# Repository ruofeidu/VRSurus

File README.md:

# VRSurus: A Tangible Virtual-Reality Game for Environmental Protection

### Introduction
We introduce VRSurus, a tangible serious game that aims to inspire children to protect the environment in immersive virtual reality (VR). VRSurus is built upon a physical puppet and a VR head-mounted display (Oculus Rift DK2) to create "tangible virtual animatronics". The player will act as a little elephant called Surus to prevent evil humanbeings from invading the forest. The player is able to use four gestures to cast magical spells: swiping left, swiping right, shaking and jumping. Servos, selonoids and vibration motors will assist with the puppet animation visible to the audience and provide haptic feedback for the player. VRSurus contributes to the HCI, animatronics and tangible computing community by integrating immersive interactive graphics together with gesture recognition and tangible feedback. The game is presented at the UIST 2015 Student Innovation Contest. Video and more details will be publicly available via www.vrsurus.com.

### Story Background
Once upon a time, there was a little elephant named Surus, living happily in a beautiful forest - Green Woodland.
However, in a cloudy day, evil human beings started to invade Green Woodland. They threw garbage everywhere; they used axes to cut down green trees; they even started to construct factories to pollute the air!
The magical elf of Green Woodland assigned you, Surus, to save the forest and rescue the nature! Surus is empowered with the magic of wind, water and fire to destroy the messy garbage, evil lumbermen and destructive factories. 

### Technical Brief
The software is built with WebGL and WebVR, which enables the game to be cross-platform for Oculus Rift and Google Cardboard. We rendered photo-realistic forest environment, GPU-based particle effects as well as skeleton-animated elephants, lumberman and factory. We use HTML5 (WebGL, WebVR, 3D Audio API), Javascript (jQuery & Three.js), GLSL ES (WebGL), PHP (ThinkPHP), MySQL and Java (Processing) to implement the entire system. 

The hardware consists of gyroscope, accelerometer, compass, servos, vibration motors, selonoids, batteries, 3D-printed skeletons and cases. 

### Authors
We the NinjaTerp team! Feel free to visit VRSurus.com for more information!
* Ruofei Du (http://duruofei.com)
   *  [Augmentarium Lab] | [UMIACS] | [University of Maryland, College Park]
   * Team Captain, Graphics (WebGL + WebVR + Model + 3D Audio) and Web Server (PHP + MySQL + Part of Java)
* Liang He (http://lianghe.me)
   * Makeability Lab | [HCIL] | [UMIACS] | [University of Maryland, College Park] 
   * Fabrication (3D Modeling, Printing), Logo, Video and Hardware (Arduino, Java)

### Advisor
* Amitabh Varshney (http://www.cs.umd.edu/~varshney)

### Presentation
The game is presented on UIST 2015 Student Innovation Contest. The project is still work-in-progress for future publications. For now, please cite
> Du, R., He, L. VRSurus: Enhancing Interactivity and Tangibility of Puppets in Virtual Reality. In Proceedings of the 33rd Annual ACM Conference Extended Abstracts on Human Factors in Computing Systems (CHI 16), 8 pages. ACM.

If you find our idea or code useful for your projects.

### How to Use
Feel free to run the entire codebase or build partial code such as only the VR game or only the open-sourced hardware.

##### VRSurus Game
The game is running a webserver with WebGL and WebVR technologies. Here is a step-by-step tutorial:
* Install [XAMPP] to setup a PHP + Apache + MySQL environment.
* Run Apache and MySQL server.
* Clone the git reporsitory and place all code into the XAMPP folder under htdocx/ninjaterp
* Open http://localhost/PHPMyAdmin, Create a new table called vrsurus and import the MySQL data from server/mysql/mysql.sql into the vrsurus table.
* Download the [Oculus Runtime] (v0.6.1 tested, v0.8 should also work) and [Chromium build for WebVR]
* Run http://localhost/ninjaterp using [Chromium build for WebVR]
* Press space on the keyboard to start the tutorial, press enter on the keyboard to start the game.
* You can control Surus using three ways:
    * Keyboard: 1, 2, 3, 4.
    * XBox: A, B, X, Y.
    * Puppet: Swipe left, swipe right, shake, thrust.

If you start the game and observe the scene flying high into the sky, then probably you are not using the correct browser: [Chromium build for WebVR]
### Instructions
##### Gecture
Please close the mouth of the puppet when performing any gesture to attack enemies. Then open the mouth.

##### Wind Spells
Swipe leftward or rightward to clean the garbage.

##### Water Spell
Shake the nose up and down to sweep the lumberman(an) away

##### Fire Spell
Punch forward to destroy the evil factories.

### Code
[Code on Github]

### Technical Challenges
This project is realy ambitious. We iterate numerous times, tried and failed in both software and hardware: anmiated models & 3D printing & miniaturization. 

### Acknowledgement
The authors would like to thank [Sai Yuan] from Department of Animal and Avian Science of [University of Maryland, College Park] for helping with splendid sewing and awesome vocal, background music and audio effects. We also thank 3DRT.com for providing a student discount for the awesome 3D models. And, thanks to [Augmentarium Lab] for funding this project.

### License
Creative Commons  Attribution-NonCommercial 4.0 International 

### Version
1.0.0

[Code on Github]: https://github.com/animatronics/ninjaterp
[Augmentarium Lab]:http://augmentarium.umiacs.umd.edu
[GVIL]:http://www.cs.umd.edu/gvil/
[HCIL]:http://www.cs.umd.edu/hcil/
[UMIACS]:http://umiacs.umd.edu
[University of Maryland, College Park]:http://www.umd.edu
[XAMPP]: https://www.apachefriends.org/index.html
[Oculus Runtime]: https://developer.oculus.com/downloads/pc/0.6.0.1-beta/Oculus_Runtime_for_Windows/
[Chromium build for WebVR]: https://drive.google.com/folderview?id=0BzudLt22BqGRbW9WTHMtOWMzNjQ
[Sai Yuan]: http://veritayuan.com/

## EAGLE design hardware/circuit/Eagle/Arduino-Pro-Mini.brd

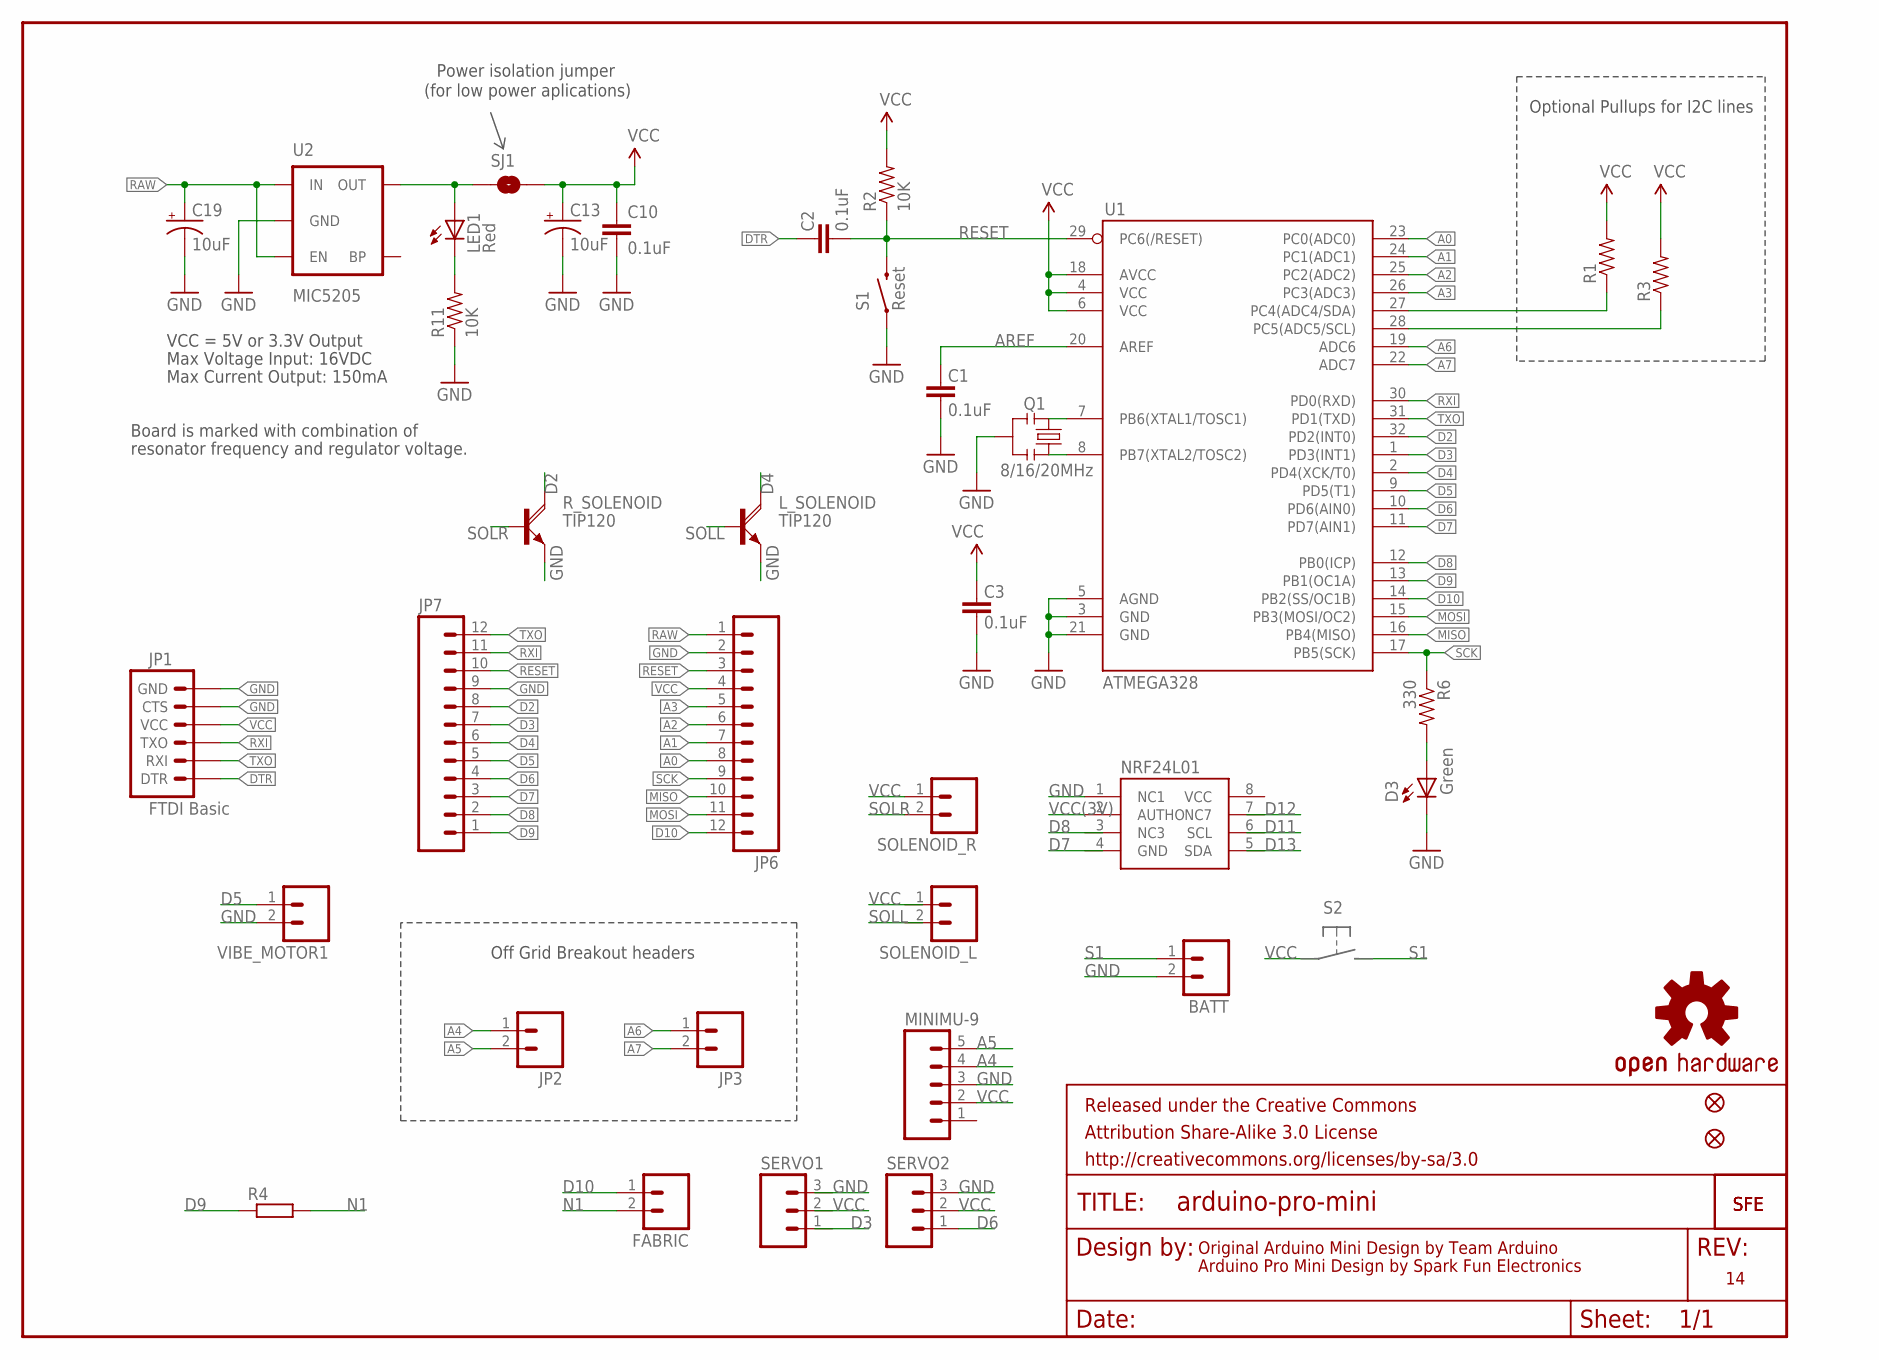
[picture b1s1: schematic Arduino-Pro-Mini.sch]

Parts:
BATT: M02PTH; 1X02
C1, C2, C3, C10: 0.1uF; 0603-CAP
C13, C19: 10uF; EIA3216
D3: Green; 0603-LED-ALT1
FABRIC: M02PTH; 1X02
FRAME1: FRAME-LETTER; CREATIVE_COMMONS
JP1: FTDI Basic; 1X06
JP2, JP3: M02PTH; 1X02
JP5, JP8: FIDUCIALUFIDUCIAL; MICRO-FIDUCIAL
JP6, JP7: M12PTH; 1X12
LED1: Red; 0603-LED-ALT1
L_SOLENOID: TIP120; TO220AH
MINIMU-9: M05; 05P
NRF24L01: ATAES132; SOIC8
Q1: 8/16/20MHz; RESONATOR-SMD-1:1
R1, R3: RESISTOR0603-RES; 0603-RES
R2, R11: 10K; 0603-RES
R4: R-EU_0204/5; 0204/5
R6: 330; 0603-RES
R_SOLENOID: TIP120; TO220AH
S1: Reset; TACTILE-SWITCH-SMD-ALT01
SERVO1, SERVO2: M03; 03P
SJ1: SOLDERJUMPERNC; SJ_2S
SOLENOID_L: M02PTH; 1X02
SOLENOID_R: M02PTH; 1X02
U1: ATMEGA328; TQFP32-08
U2: MIC5205; SOT23-5
U$1: LOGO-SFESK; SFE-LOGO-FLAME
U$3: OSHW-LOGOS; OSHW-LOGO-S
U$11: LOGO-SFENEW; SFE-NEW-WEBLOGO
VIBE_MOTOR1: M02PTH; 1X02

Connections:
A0: JP6.8, U1.23 (PC0(ADC0))
A1: JP6.7, U1.24 (PC1(ADC1))
A2: JP6.6, U1.25 (PC2(ADC2))
A3: JP6.5, U1.26 (PC3(ADC3))
A4: JP2.1, MINIMU-9.4, R1.1, U1.27 (PC4(ADC4/SDA))
A5: JP2.2, MINIMU-9.5, R3.1, U1.28 (PC5(ADC5/SCL))
A6: JP3.1, U1.19 (ADC6)
A7: JP3.2, U1.22 (ADC7)
AREF: C1.2, U1.20 (AREF)
D2: JP7.8, R_SOLENOID.C, U1.32 (PD2(INT0))
D3: JP7.7, U1.1 (PD3(INT1))
D4: JP7.6, L_SOLENOID.C, U1.2 (PD4(XCK/T0))
D5: JP7.5, U1.9 (PD5(T1)), VIBE_MOTOR1.1
D6: JP7.4, SERVO2.1, U1.10 (PD6(AIN0))
D7: JP7.3, U1.11 (PD7(AIN1))
D8: JP7.2, U1.12 (PB0(ICP))
D9: JP7.1, R4.1, U1.13 (PB1(OC1A))
D10: FABRIC.1, JP6.12, U1.14 (PB2(SS/OC1B))
DTR: C2.2, JP1.1 (DTR)
GND: BATT.2, C1.1, C3.1, C10.2, C13.C (-), C19.C (-), D3.C, JP1.5 (CTS), JP1.6 (GND), JP6.2, JP7.9, L_SOLENOID.E, MINIMU-9.3, NRF24L01.1 (NC1), NRF24L01.4 (GND), Q1.2, R11.1, R_SOLENOID.E, S1.1, S1.2 (1), SERVO2.3, U1.3 (GND), U1.5 (AGND), U1.21 (GND), U2.2 (GND), VIBE_MOTOR1.2
MISO: JP6.10, U1.16 (PB4(MISO))
MOSI: JP6.11, U1.15 (PB3(MOSI/OC2))
N1: FABRIC.2, R4.2
unnamed: Q1.3, U1.8 (PB7(XTAL2/TOSC2))
unnamed: Q1.1, U1.7 (PB6(XTAL1/TOSC1))
unnamed: LED1.A, SJ1.1, U2.5 (OUT)
unnamed: LED1.C, R11.2
unnamed: D3.A, R6.2
RAW: C19.A (+), JP6.1, U2.1 (IN), U2.3 (EN)
RESET: C2.1, JP6.3, JP7.10, R2.1, S1.3 (2), S1.4 (2), U1.29 (PC6(/RESET))
RXI: JP1.3 (TXO), JP7.11, U1.30 (PD0(RXD))
S1: BATT.1
SCK: JP6.9, R6.1, U1.17 (PB5(SCK))
SOLL: L_SOLENOID.B
SOLR: R_SOLENOID.B, SOLENOID_R.2
TXO: JP1.2 (RXI), JP7.12, U1.31 (PD1(TXD))
VCC: C3.2, C10.1, C13.A (+), JP1.4 (VCC), JP6.4, MINIMU-9.2, NRF24L01.8 (VCC), R1.2, R2.2, R3.2, SERVO2.2, SJ1.2, SOLENOID_R.1, U1.4 (VCC), U1.6 (VCC), U1.18 (AVCC)
VCC(3V): NRF24L01.2 (AUTHO)

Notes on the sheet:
Original Arduino Mini Design by Team Arduino
Arduino Pro Mini Design by Spark Fun Electronics
Max Voltage Input: 16VDC
Max Current Output: 150mA
Board is marked with combination of
resonator frequency and regulator voltage.
VCC = 5V or 3.3V Output
Optional Pullups for I2C lines
Off Grid Breakout headers
Power isolation jumper
(for low power aplications)

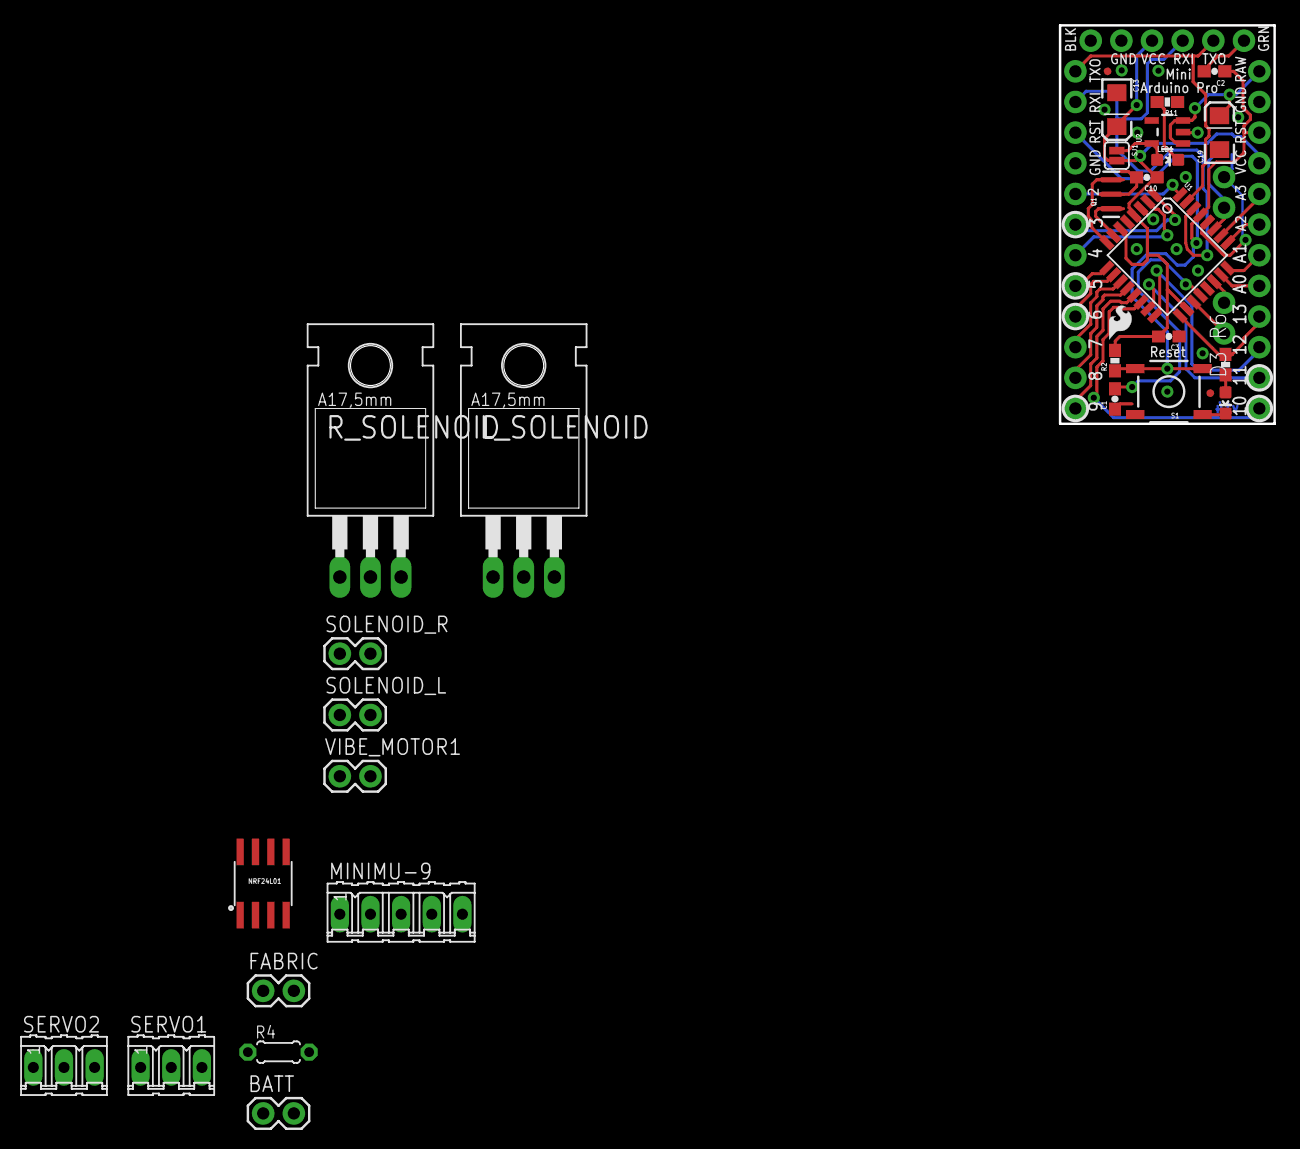
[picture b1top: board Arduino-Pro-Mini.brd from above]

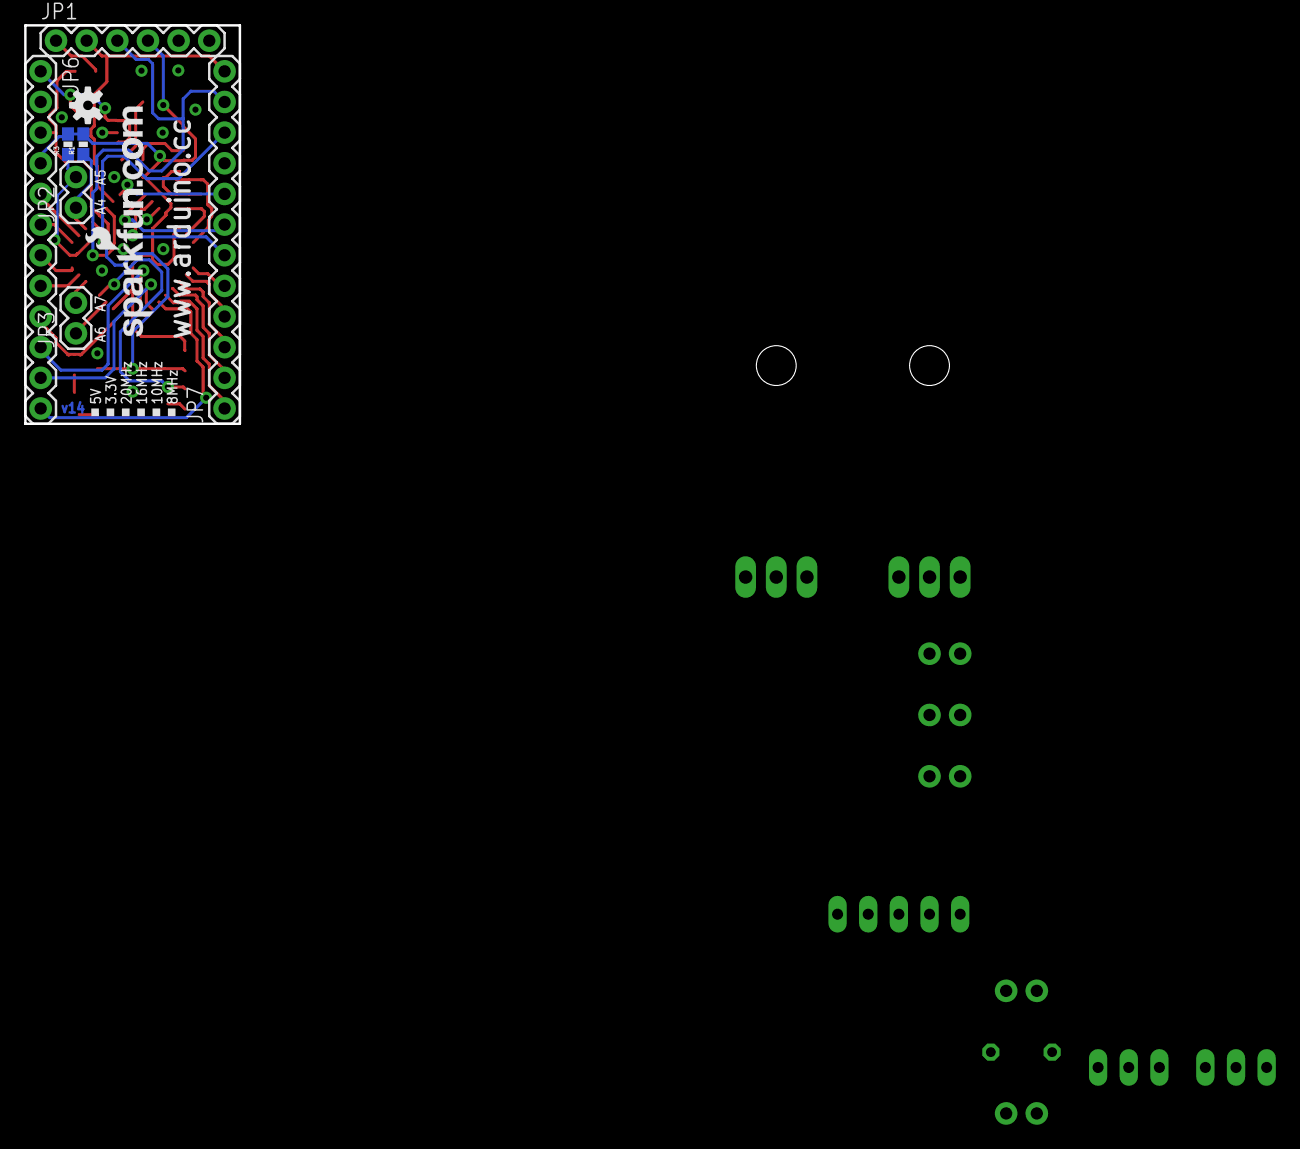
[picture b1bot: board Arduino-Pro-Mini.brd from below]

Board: 2 copper layers, 17.8 x 33.0 mm, 41 parts (9 on the bottom side), 35 nets.

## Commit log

2015-09-28 add README
2015-09-28 Added design and hardware
2015-10-15 First version: animated Springer, one weekends' work.
2015-10-15 Add license
2015-10-15 Add changelog
2015-10-15 Add contribution guide
2015-10-15 add debug info
2015-10-24 Surus
2015-10-24 Added VR control and key control.
2015-10-25 added sound, adjusted camera position for VR.
2015-10-26 audio
2015-10-30 working on lots of things in parallel..
2015-10-30 skysphere added.
2015-10-31 trees pending.
2015-10-31 trees
2015-10-31 trees done!!!
2015-10-31 before dinner.
2015-11-01 water almost done.
2015-11-01 spray done. 5 actions defined.
2015-11-01 5 actions done.
2015-11-02 factory done
2015-11-02 fix the loader
2015-11-02 garbage added.
2015-11-02 refracted models and particles.
2015-11-02 add gaming process, die and vanish, yeah!
2015-11-03 game is playable, yeah!!!
2015-11-03 add gamepad support.
2015-11-03 all game component completed.
2015-11-04 add server script via thinkPHP.
2015-11-04 web server and test case done.
2015-11-04 add test.php
2015-11-04 add models.
2015-11-05 game over animation etc.
2015-11-05 score sprite.
2015-11-06 score sprite done.
2015-11-06 add audio files.
2015-11-06 game over.
2015-11-06 three two one go
2015-11-06 fix game over bug, add tutorial pictures.
2015-11-07 smoke and resolve two bugs for xbox controller and for black screen error.
2015-11-07 audio added.
2015-11-07 add instruction audios.
2015-11-07 update readme signals.
2015-11-07 signals
2015-11-07 open-sourced hardware, 3D printed models added. Final version before the trip!
2017-12-15 git attribute update
2017-12-15 updated .gitattributes

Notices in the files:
parts and their libraries:
SparkFun-Aesthetics: Licensing: CC v3.0 Share-Alike You are welcome to use this library for commercial purposes.
SparkFun-Aesthetics: Released under the Creative Commons Attribution Share-Alike 3.0 License
SparkFun-Aesthetics: http://creativecommons.org/licenses/by-sa/3.0
